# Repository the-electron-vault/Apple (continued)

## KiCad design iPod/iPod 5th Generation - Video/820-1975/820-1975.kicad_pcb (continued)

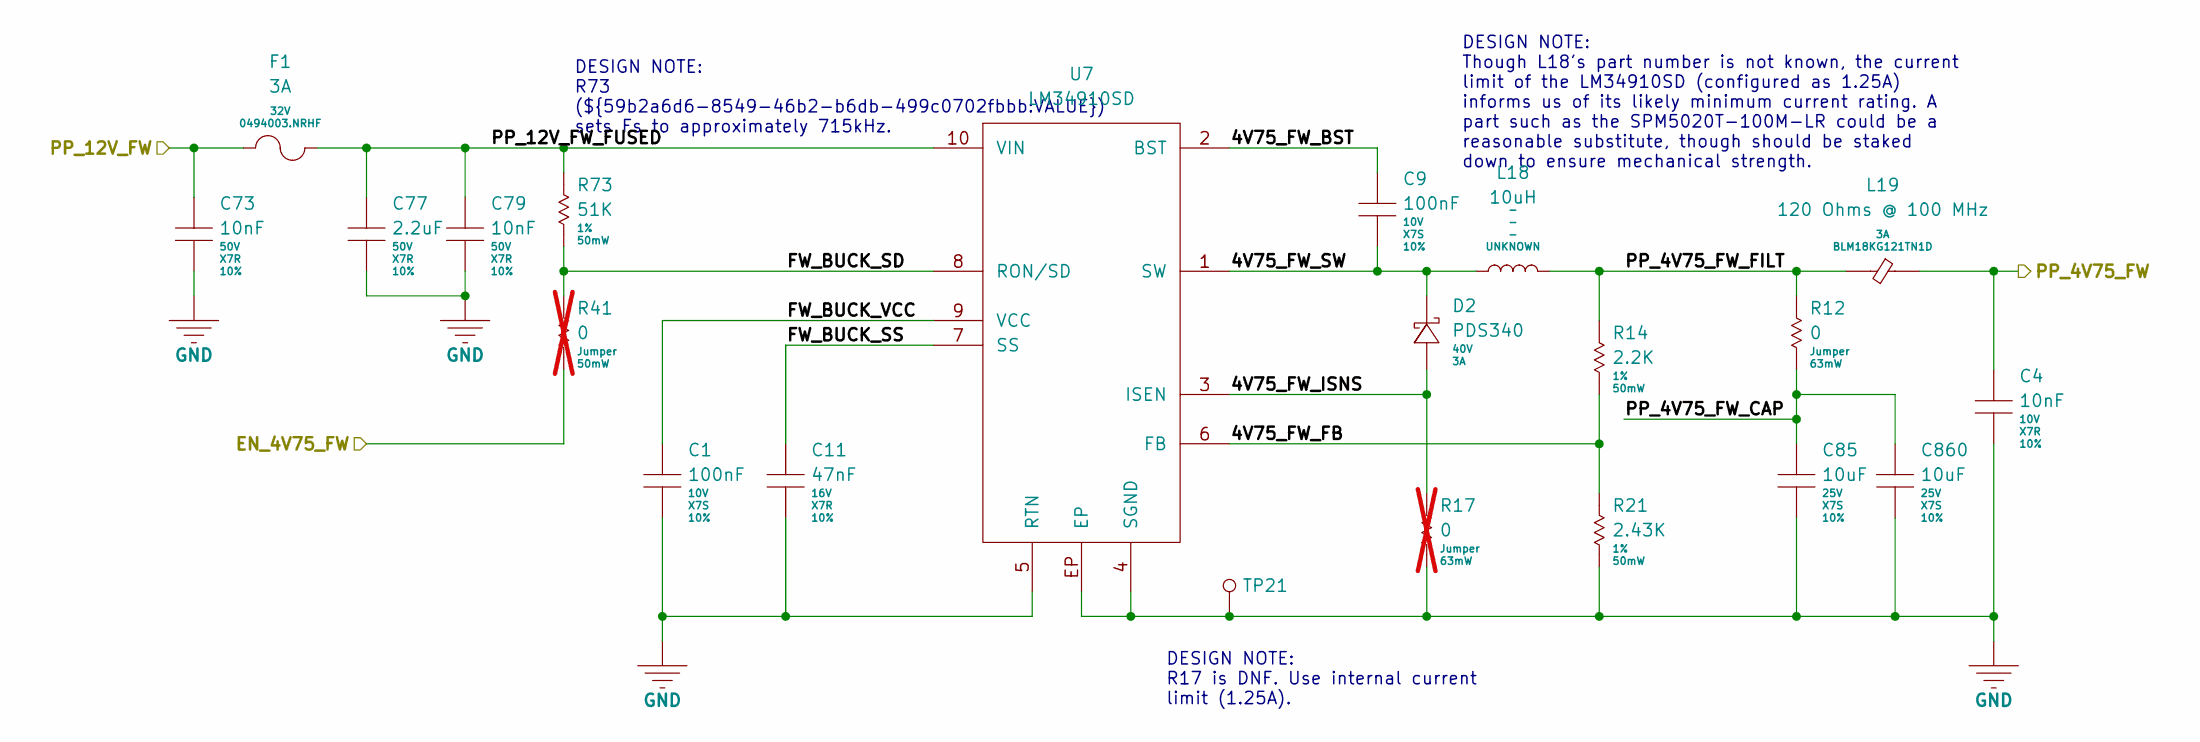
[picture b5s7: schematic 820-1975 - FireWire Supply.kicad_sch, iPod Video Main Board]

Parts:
C1, C9: 100nF; MLCC-0201; Voltage 10V; Tolerance 10%; Manufacturer Part Number GRM033C71A104KE14D
C4: 10nF; MLCC-0201; Voltage 10V; Tolerance 10%; Manufacturer Part Number GRM033R71A103KA01D
C11: 47nF; MLCC-0402; Voltage 16V; Tolerance 10%; Manufacturer Part Number GCM155R71C473KA37D
C73, C79: 10nF; MLCC-0603; Voltage 50V; Tolerance 10%; Manufacturer Part Number GCM188R71H103KA37D
C77: 2.2uF; MLCC-1206; Voltage 50V; Tolerance 10%; Manufacturer Part Number GCM31CR71H225KA55L
C85, C860: 10uF; MLCC-0805; Voltage 25V; Tolerance 10%; Manufacturer Part Number GRM21BC71E106KE11L
D2: PDS340; PowerDI-5; Voltage 40V; Manufacturer Part Number PDS340
F1: 3A; FUSE-0603; Voltage 32V; Manufacturer Part Number 0494003.NRHF
L18: 10uH; SUMIDA-UNKNOWN; Manufacturer Part Number UNKNOWN
L19: 120 Ohms @ 100 MHz; FB-0603; Manufacturer Part Number BLM18KG121TN1D
R12: 0; RES-0402; Tolerance Jumper; Manufacturer Part Number CRCW04020000Z0ED
R14: 2.2K; RES-0201; Tolerance 1%; Manufacturer Part Number CRCW02012K20FNED
R17: 0; RES-0402; Tolerance Jumper; Manufacturer Part Number CRCW04020000Z0ED; not fitted
R21: 2.43K; RES-0201; Tolerance 1%; Manufacturer Part Number CRCW02012K43FNED
R41: 0; RES-0201; Tolerance Jumper; Manufacturer Part Number CRCW02010000Z0ED; not fitted
R73: 51K; RES-0201; Tolerance 1%; Manufacturer Part Number CRCW020151K0FNED
TP21: TP; TP-SMT
U7: LM34910SD; DPR0010A; Manufacturer Part Number LM34910SD

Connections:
/Charger-and-3.3V-Supply/PP_4V75_FW: C4.1, L19.2; also elsewhere on the board
/Dock-Interface/PP_12V_FW: C73.1, F1.1; also elsewhere on the board
/FireWire-Supply/4V75_FW_BST: C9.1, U7.2 (BST)
/FireWire-Supply/4V75_FW_FB: R14.2, R21.1, U7.6 (FB)
/FireWire-Supply/4V75_FW_ISNS: D2.A, R17.1, U7.3 (ISEN)
/FireWire-Supply/4V75_FW_SW: C9.2, D2.K, L18.1, U7.1 (SW)
/FireWire-Supply/EN_4V75_FW: R41.2; also elsewhere on the board
/FireWire-Supply/FW_BUCK_SD: R41.1, R73.2, U7.8 (RON/SD)
/FireWire-Supply/FW_BUCK_SS: C11.1, U7.7 (SS)
/FireWire-Supply/FW_BUCK_VCC: C1.1, U7.9 (VCC)
/FireWire-Supply/PP_4V75_FW_CAP: C85.1, C860.1, R12.2
/FireWire-Supply/PP_4V75_FW_FILT: L18.2, L19.1, R12.1, R14.1
/FireWire-Supply/PP_12V_FW_FUSED: C77.1, C79.1, F1.2, R73.1, U7.10 (VIN)
GND: C1.2, C4.2, C11.2, C73.2, C77.2, C79.2, C85.2, C860.2, R17.2, R21.2, TP21.1, U7.4 (SGND), U7.5 (RTN), U7.EP; also elsewhere on the board

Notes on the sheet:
DESIGN NOTE: R73 (${59b2a6d6-8549-46b2-b6db-499c0702fbbb:VALUE}) sets Fs to approximately 715kHz.
DESIGN NOTE: R17 is DNF. Use internal current limit (1.25A).
DESIGN NOTE: Though L18's part number is not known, the current limit of the LM34910SD (configured as 1.25A) informs us of its likely minimum current rating. A part such as the SPM5020T-100M-LR could be a reasonable substitute, though should be staked down to ensure mechanical strength.

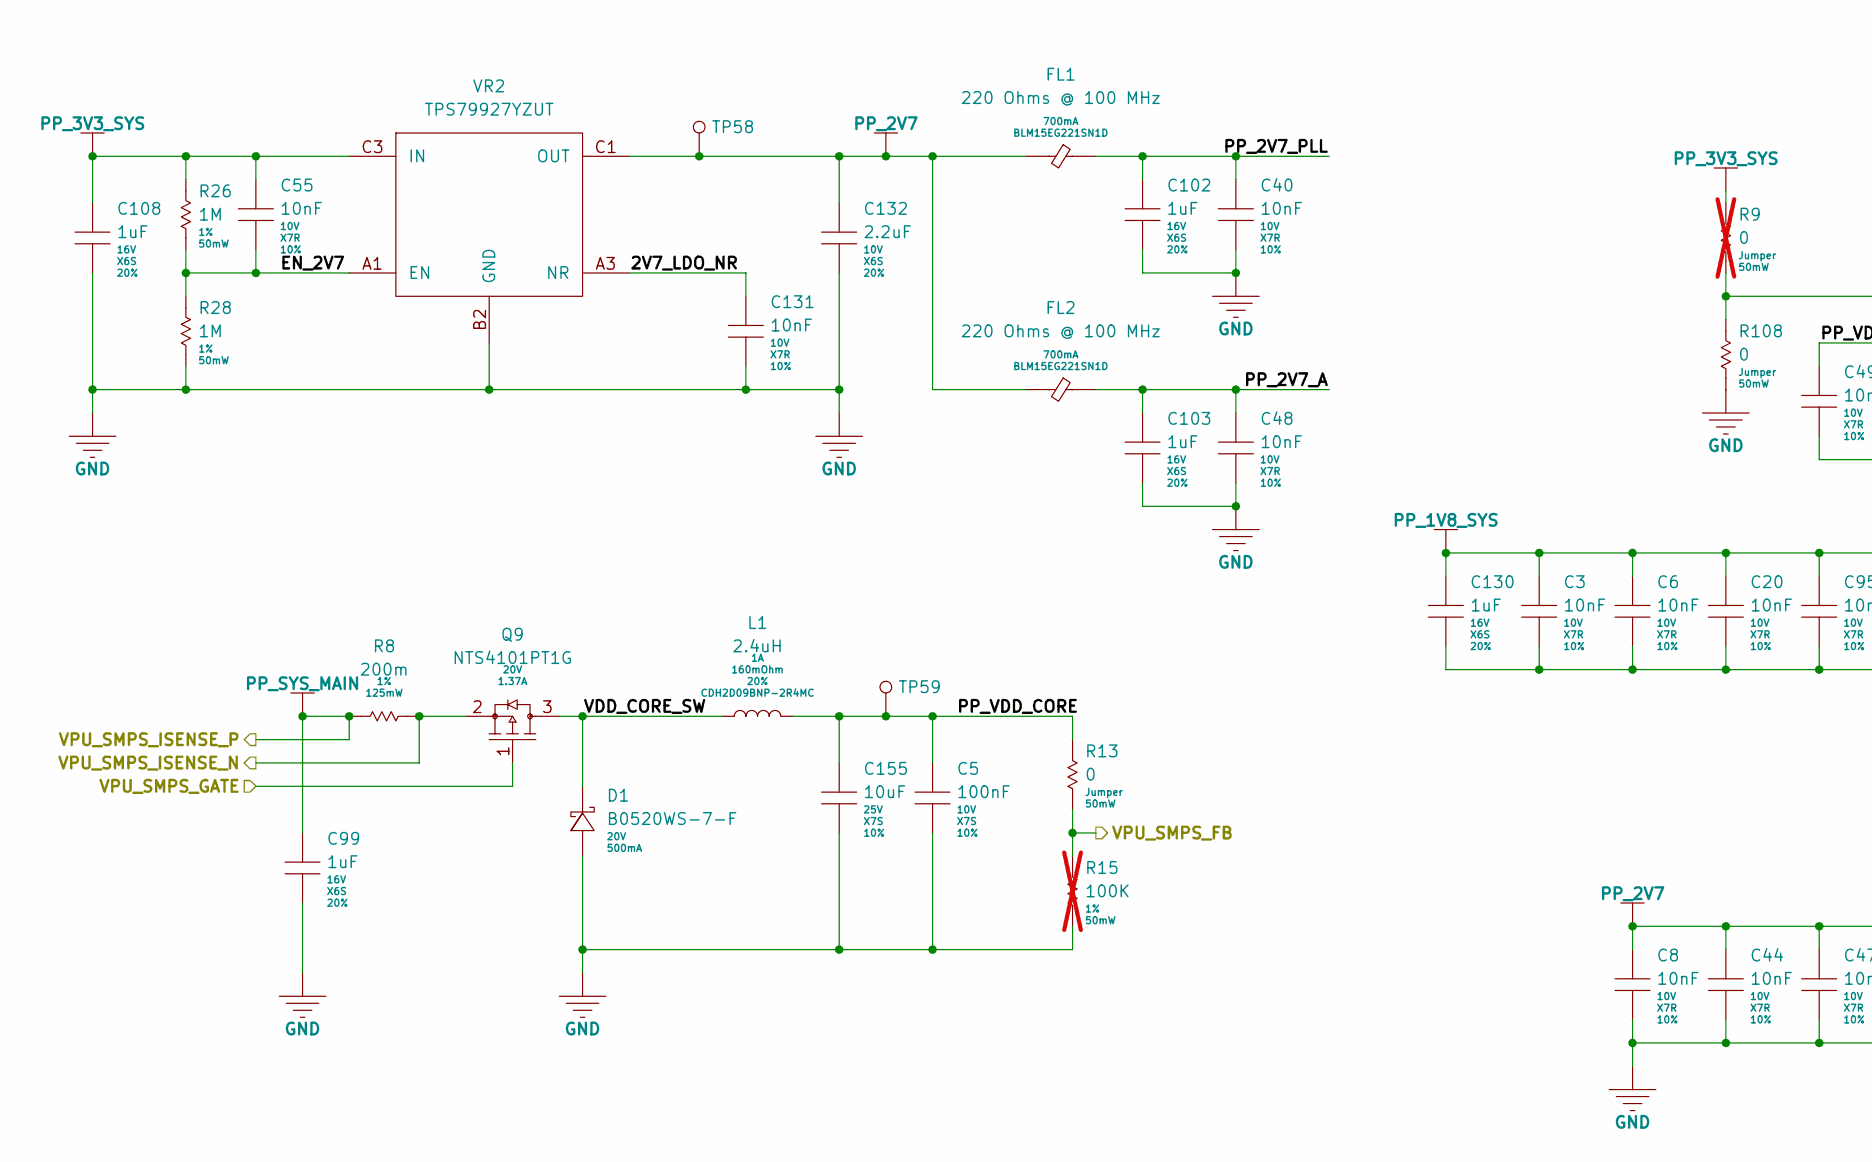
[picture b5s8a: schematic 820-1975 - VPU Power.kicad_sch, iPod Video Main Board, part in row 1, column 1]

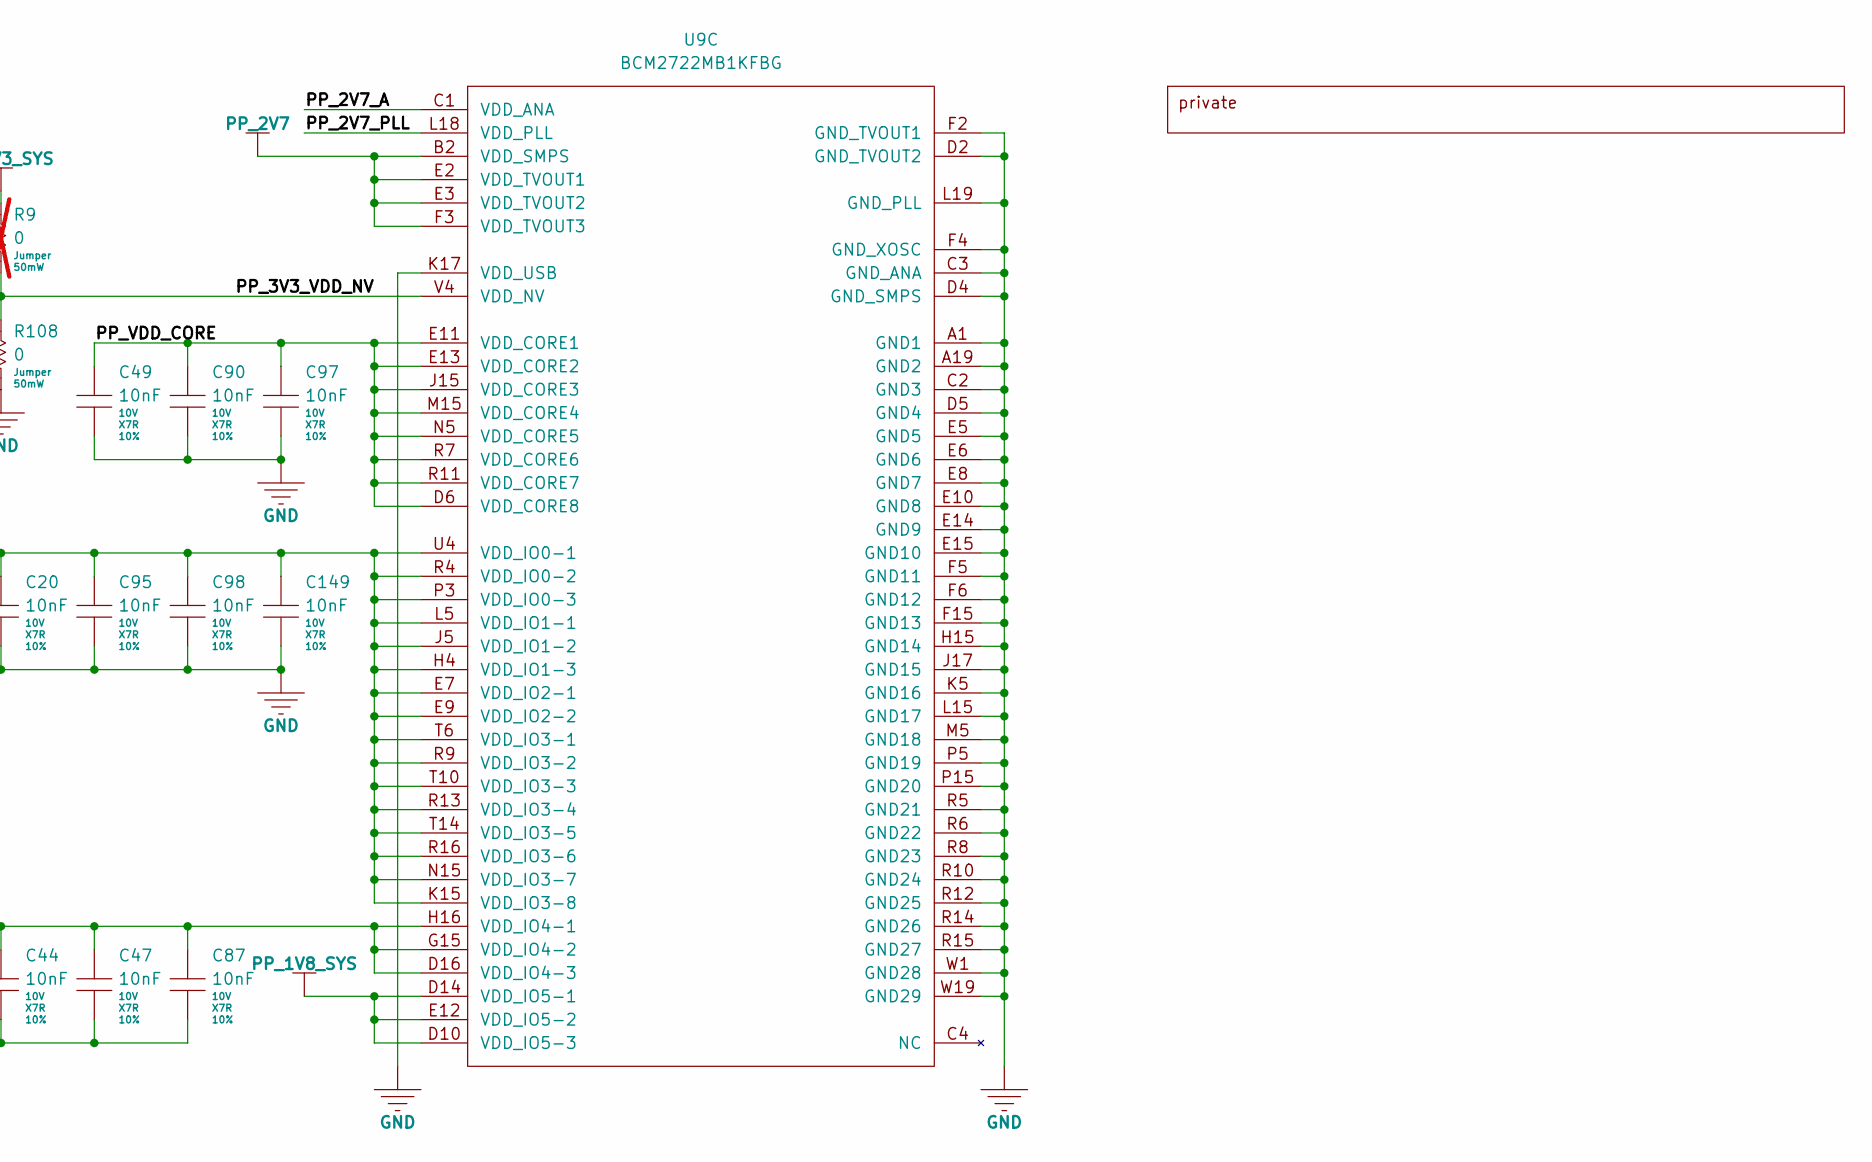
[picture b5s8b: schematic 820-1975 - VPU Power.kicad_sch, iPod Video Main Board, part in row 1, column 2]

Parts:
C3, C6, C8, C20, C40, C44, C47, C48, C49, C55, C87, C90, C95, C97, C98, C131, C149: 10nF; MLCC-0201; Voltage 10V; Tolerance 10%; Manufacturer Part Number GRM033R71A103KA01D
C5: 100nF; MLCC-0201; Voltage 10V; Tolerance 10%; Manufacturer Part Number GRM033C71A104KE14D
C99, C102, C103, C108, C130: 1uF; MLCC-0402; Voltage 16V; Tolerance 20%; Manufacturer Part Number GRM155C81C105ME11J
C132: 2.2uF; MLCC-0402; Voltage 10V; Tolerance 20%; Manufacturer Part Number GRM155C81A225ME44D
C155: 10uF; MLCC-0805; Voltage 25V; Tolerance 10%; Manufacturer Part Number GRM21BC71E106KE11L
D1: B0520WS-7-F; SOD-323; Voltage 20V; Manufacturer Part Number B0520WS-7-F
FL1, FL2: 220 Ohms @ 100 MHz; FB-0402; Manufacturer Part Number BLM15EG221SN1D
L1: 2.4uH; CDH2D09B; Tolerance 20%; Manufacturer Part Number CDH2D09BNP-2R4MC
Q9: NTS4101PT1G; SOT-323; Voltage 20V; Manufacturer Part Number NTS4101PT1G
R8: 200m; RES-0402; Tolerance 1%; Manufacturer Part Number RCWE0402R200FKEA
R9: 0; RES-0201; Tolerance Jumper; Manufacturer Part Number CRCW02010000Z0ED; not fitted
R13, R108: 0; RES-0201; Tolerance Jumper; Manufacturer Part Number CRCW02010000Z0ED
R15: 100K; RES-0201; Tolerance 1%; Manufacturer Part Number CRCW0201100KFNED; not fitted
R26, R28: 1M; RES-0201; Tolerance 1%; Manufacturer Part Number CRCW02011M00FNED
TP58, TP59: TP; TP-SMT
U9: BCM2722MB1KFBG; Manufacturer Part Number BCM2722MB1KFBG
VR2: TPS79927YZUT; TI-YZU0005; Manufacturer Part Number TPS79927YZUT

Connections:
/VPU-Power/2V7_LDO_NR: C131.1, VR2.A3 (NR)
/VPU-Power/EN_2V7: C55.2, R26.2, R28.1, VR2.A1 (EN)
/VPU-Power/PP_2V7_A: C48.1, C103.1, FL2.2, U9.C1 (VDD_ANA)
/VPU-Power/PP_2V7_PLL: C40.1, C102.1, FL1.2, U9.L18 (VDD_PLL)
/VPU-Power/PP_3V3_VDD_NV: R9.2, R108.1, U9.V4 (VDD_NV)
/VPU-Power/PP_VDD_CORE: C5.1, C49.1, C90.1, C97.1, C155.1, L1.2, R13.1, TP59.1, U9.D6 (VDD_CORE8), U9.E11 (VDD_CORE1), U9.E13 (VDD_CORE2), U9.J15 (VDD_CORE3), U9.M15 (VDD_CORE4), U9.N5 (VDD_CORE5), U9.R7 (VDD_CORE6), U9.R11 (VDD_CORE7)
/VPU-Power/VDD_CORE_SW: D1.K, L1.1, Q9.3 (D)
/VPU-Power/VPU_SMPS_FB: R13.2, R15.1; also elsewhere on the board
/VPU-Power/VPU_SMPS_GATE: Q9.1 (G); also elsewhere on the board
/VPU-Power/VPU_SMPS_ISENSE_N: Q9.2 (S), R8.2; also elsewhere on the board
GND: C3.2, C5.2, C6.2, C8.2, C20.2, C40.2, C44.2, C47.2, C48.2, C49.2, C87.2, C90.2, C95.2, C97.2, C98.2, C99.2, C102.2, C103.2, C108.2, C130.2, C131.2, C132.2, C149.2, C155.2, D1.A, R15.2, R28.2, R108.2, U9.A1 (GND1), U9.A19 (GND2), U9.C2 (GND3), U9.C3 (GND_ANA), U9.D2 (GND_TVOUT2), U9.D4 (GND_SMPS), U9.D5 (GND4), U9.E5 (GND5), U9.E6 (GND6), U9.E8 (GND7), U9.E10 (GND8), U9.E14 (GND9), U9.E15 (GND10), U9.F2 (GND_TVOUT1), U9.F4 (GND_XOSC), U9.F5 (GND11), U9.F6 (GND12), U9.F15 (GND13), U9.H15 (GND14), U9.J17 (GND15), U9.K5 (GND16), U9.K17 (VDD_USB), U9.L15 (GND17), U9.L19 (GND_PLL), U9.M5 (GND18), U9.P5 (GND19), U9.P15 (GND20), U9.R5 (GND21), U9.R6 (GND22), U9.R8 (GND23), U9.R10 (GND24), U9.R12 (GND25), U9.R14 (GND26), U9.R15 (GND27), U9.W1 (GND28), U9.W19 (GND29), VR2.B2 (GND); also elsewhere on the board
PP_1V8_SYS: C3.1, C6.1, C20.1, C95.1, C98.1, C130.1, C149.1, U9.D10 (VDD_IO5-3), U9.D14 (VDD_IO5-1), U9.E7 (VDD_IO2-1), U9.E9 (VDD_IO2-2), U9.E12 (VDD_IO5-2), U9.H4 (VDD_IO1-3), U9.J5 (VDD_IO1-2), U9.K15 (VDD_IO3-8), U9.L5 (VDD_IO1-1), U9.N15 (VDD_IO3-7), U9.P3 (VDD_IO0-3), U9.R4 (VDD_IO0-2), U9.R9 (VDD_IO3-2), U9.R13 (VDD_IO3-4), U9.R16 (VDD_IO3-6), U9.T6 (VDD_IO3-1), U9.T10 (VDD_IO3-3), U9.T14 (VDD_IO3-5), U9.U4 (VDD_IO0-1); also elsewhere on the board
PP_2V7: C8.1, C44.1, C47.1, C87.1, C132.1, FL1.1, FL2.1, TP58.1, U9.B2 (VDD_SMPS), U9.D16 (VDD_IO4-3), U9.E2 (VDD_TVOUT1), U9.E3 (VDD_TVOUT2), U9.F3 (VDD_TVOUT3), U9.G15 (VDD_IO4-2), U9.H16 (VDD_IO4-1), VR2.C1 (OUT); also elsewhere on the board
PP_3V3_SYS: C55.1, C108.1, R9.1, R26.1, VR2.C3 (IN); also elsewhere on the board
PP_SYS_MAIN: C99.1, R8.1; also elsewhere on the board

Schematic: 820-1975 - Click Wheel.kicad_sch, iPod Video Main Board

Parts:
C39, C41: 100nF; MLCC-0201; Voltage 10V; Tolerance 10%; Manufacturer Part Number GRM033C71A104KE14D
C52: 1nF; MLCC-0201; Voltage 25V; Tolerance 10%; Manufacturer Part Number GRM033R71E102KA01J
C141: 4.7uF; MLCC-0603; Voltage 10V; Tolerance 10%; Manufacturer Part Number GRM188C71A475KE11D
J5: FF12-13A-R11AL-3H; Manufacturer Part Number FF12-13A-R11AL-3H
Q5: BSS84DW-7-F; SOT-363; Voltage 50V; Manufacturer Part Number BSS84DW-7-F
R2: 1M; RES-0201; Tolerance 1%; Manufacturer Part Number CRCW02011M00FNED
R3: 2.2M; RES-0201; Tolerance 1%; Manufacturer Part Number CRCW02012M20FNED
R44: 100K; RES-0201; Tolerance 1%; Manufacturer Part Number CRCW0201100KFNED
R61: 10K; RES-0201; Tolerance 1%; Manufacturer Part Number CRCW020110K0FNED
R86: 0; RES-0201; Tolerance Jumper; Manufacturer Part Number CRCW02010000Z0ED; not fitted
R87: 220K; RES-0201; Tolerance 1%; Manufacturer Part Number CRCW0201220KFNED
R97: 0; RES-0201; Tolerance Jumper; Manufacturer Part Number CRCW02010000Z0ED
R100, R101, R102, R103: 18K; RES-0201; Tolerance 1%; Manufacturer Part Number CRCW020118K0FKED
R142: 10; RES-0201; Tolerance 1%; Manufacturer Part Number CRCW020110R0FNED
S100, S101, S102, S103, S104: SOP-112HST; SOP-11xHST; Manufacturer Part Number SOP-112HST
TP87, TP88, TP89, TP90, TP91, TP92, TP93, TP94, TP95, TP96, TP97, TP98, TP99, TP100, TP101: TP; TP-SMT
U19: SN74LVC1G32YZPR; TI-YZP0005; Manufacturer Part Number SN74LVC1G32YZPR

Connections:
/CODEC/HOLD: C52.1, R3.1, R44.1; also elsewhere on the board
/Charger-and-3.3V-Supply/RESET_SYS: C41.1, R61.1; also elsewhere on the board
/Click-Wheel/BTN_FF_L: J5.5, S103.3, S103.4, TP96.1
/Click-Wheel/BTN_MENU_L: J5.4, S102.3, S102.4, TP97.1
/Click-Wheel/BTN_PP_L: J5.6, S104.3, S104.4, TP95.1
/Click-Wheel/BTN_RW_L: J5.3, S101.3, S101.4, TP98.1
/Click-Wheel/BTN_SEL_L: J5.2, S100.3, S100.4, TP99.1
/Click-Wheel/CW_CLK: U19.4 (Y); also elsewhere on the board
/Click-Wheel/CW_GATE_CLK: J5.12, R101.2, TP89.1, U19.1 (A)
/Click-Wheel/CW_PIN7: J5.7, R102.2, TP94.1; also elsewhere on the board
/Click-Wheel/CW_SDI: J5.8, R103.2, TP93.1; also elsewhere on the board
/Click-Wheel/CW_SDO: J5.11, R100.2, TP90.1; also elsewhere on the board
/Click-Wheel/EN_CW_PWR_L: Q5.2 (G1), Q5.5 (G2), R44.2
/Click-Wheel/PMU_EXTON: J5.10, TP91.1; also elsewhere on the board
/Click-Wheel/PP_VDDIO_CW_FET: Q5.4 (S2), R86.2, R97.2
/Click-Wheel/PP_VDD_CW: Q5.6 (D1), R142.1
/Click-Wheel/PP_VDD_CW_CONN: C141.1, J5.13, R142.2, TP87.1
/Click-Wheel/RESET_SYS_CW: J5.9, R61.2, R87.1, TP92.1
GND: C39.2, C41.2, C52.2, C141.2, J5.1, R2.2, R3.2, R87.2, S100.1, S100.2, S101.1, S101.2, S102.1, S102.2, S103.1, S103.2, S104.1, S104.2, TP100.1, TP101.1, U19.2 (B), U19.3 (GND); also elsewhere on the board
PP_3V3_SYS: C39.1, R86.1, U19.5 (VCC); also elsewhere on the board
PP_3V_LCD: R97.1; also elsewhere on the board
PP_SYS_MAIN: Q5.1 (S1); also elsewhere on the board
PP_VDDIO_CW: Q5.3 (D2), R2.1, R100.1, R101.1, R102.1, R103.1, TP88.1; also elsewhere on the board

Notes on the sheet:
DESIGN NOTE: CW_SDO only outputs data when shorted to CW_SDI (when operating clickwheel standalone). The purpose of J5-7 is not known.
DESIGN NOTE: RESET_SYS_CW pulses high for 500ms when Menu and Select are held for 5 seconds. Menu button *must* detect finger on clickwheel. Simply pressing the underlying buttons is not sufficient. PMU_EXTON pulses high for 20ms when Menu or Select is pressed.

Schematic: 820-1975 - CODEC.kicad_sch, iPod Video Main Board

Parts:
C42, C127, C148: 10nF; MLCC-0201; Voltage 10V; Tolerance 10%; Manufacturer Part Number GRM033R71A103KA01D
C84, C86, C100, C101: 10uF; KYOCERA-TAC-L; Voltage 6.3V; Tolerance 20%; Manufacturer Part Number TACL106M006RTA
C89, C925, C926: 100nF; MLCC-0201; Voltage 10V; Tolerance 10%; Manufacturer Part Number GRM033C71A104KE14D
C96: 4.7uF; MLCC-0603; Voltage 10V; Tolerance 10%; Manufacturer Part Number GRM188C71A475KE11D
C138: 2.2uF; MLCC-0603; Voltage 25V; Tolerance 10%; Manufacturer Part Number GRM188C71E225KE11D
C140, C150: 4.7uF; VISHAY-TMCJ; Voltage 6.3V; Tolerance 20%; Manufacturer Part Number TMCJ0J475MTRF
C145, C146: 150uF; VISHAY-595D-B; Voltage 4V; Tolerance 20%; Manufacturer Part Number 595D157X0004B2T
J1: FH26W-13S-0.3SHW; Manufacturer Part Number FH26W-13S-0.3SHW
Q2: MMDT3946-7-F; SOT-363; Voltage 40V; Manufacturer Part Number MMDT3946-7-F
R23, R123: 0; RES-0201; Tolerance Jumper; Manufacturer Part Number CRCW02010000Z0ED; not fitted
R24: 10K; RES-0201; Tolerance 1%; Manufacturer Part Number CRCW020110K0FNED
R39, R129: 0; RES-0201; Tolerance Jumper; Manufacturer Part Number CRCW02010000Z0ED
R84: 33; RES-0201; Tolerance 1%; Manufacturer Part Number CRCW020133R0FNED
R133: 1M; RES-0201; Tolerance 1%; Manufacturer Part Number CRCW02011M00FNED
R134, R194, R195, R196, R197: 100K; RES-0201; Tolerance 1%; Manufacturer Part Number CRCW0201100KFNED
R146: 1K; RES-0201; Tolerance 1%; Manufacturer Part Number CRCW02011K00FNED
R147: 270; RES-0201; Tolerance 1%; Manufacturer Part Number CRCW0201270RFKED
R190, R191, R192, R193: 100; RES-0201; Tolerance 1%; Manufacturer Part Number CRCW0201100RFKED
R915: 47; RES-0201; Tolerance 1%; Manufacturer Part Number CRCW020147R0FNED
TP102, TP103, TP104, TP105, TP106, TP107: TP; TP-SMT
U5: WM8758CBGEFL; Manufacturer Part Number WM8758CBGEFL
U8, U13, U14: SN74LVC1G32YZPR; TI-YZP0005; Manufacturer Part Number SN74LVC1G32YZPR

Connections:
/CODEC/AUDCONN_TIPDET: C138.1, R133.2, R134.1; also elsewhere on the board
/CODEC/AUDCONN_TIPDET_SW: J1.1, R134.2, TP102.1
/CODEC/AUDCONN_VID_COMP: J1.10; also elsewhere on the board
/CODEC/CODEC_CSB: R123.2, R129.1, U5.15 (CSB)
/CODEC/CODEC_MCLK: R84.1; also elsewhere on the board
/CODEC/CODEC_MCLK_R: R84.2, TP105.1, U5.11 (MCLK)
/CODEC/CODEC_VMID: C96.1, U5.27 (VMID)
/CODEC/EN_I2S_VPU_L: R23.1; also elsewhere on the board
/CODEC/EN_I2S_VPU_R_L: R23.2, R39.1, U8.2 (B), U13.2 (B)
/CODEC/HOLD: J1.13, TP106.1; also elsewhere on the board
/CODEC/HOLD_SW_PU: J1.12, R24.2, TP104.1
/CODEC/HP_COM: C150.1, U5.19 (HP_COM)
/CODEC/HP_COM_CONN: C150.2, J1.8
/CODEC/HP_L: C145.1, U5.30 (LOUT1)
/CODEC/HP_L_CONN: C145.2, J1.5
/CODEC/HP_R: C146.1, U5.29 (ROUT1)
/CODEC/HP_R_CONN: C146.2, J1.6
/CODEC/I2C_SCL: U5.16 (SCLK); also elsewhere on the board
/CODEC/I2C_SDA: U5.17 (SDIN); also elsewhere on the board
/CODEC/I2S_DOUT: U5.10 (DACDAT), U14.4 (Y)
/CODEC/I2S_MPU_BCLK: U5.8 (BCLK), U13.1 (A); also elsewhere on the board
/CODEC/I2S_MPU_DIN: U5.9 (ADCDAT); also elsewhere on the board
/CODEC/I2S_MPU_DOUT: U14.2 (B); also elsewhere on the board
/CODEC/I2S_MPU_LRC: U5.7 (LRC), U8.1 (A); also elsewhere on the board
/CODEC/I2S_VPU_BCLK: U13.4 (Y); also elsewhere on the board
/CODEC/I2S_VPU_DOUT: U14.1 (A); also elsewhere on the board
/CODEC/I2S_VPU_LRC: U8.4 (Y); also elsewhere on the board
/CODEC/LINEIN_CAP_L: C101.2, R192.1, R195.1
/CODEC/LINEIN_CAP_R: C100.2, R193.1, R194.1
/CODEC/LINEIN_L: R192.2; also elsewhere on the board
/CODEC/LINEIN_R: R193.2; also elsewhere on the board
/CODEC/LINEOUT_CAP_L: C86.2, R190.1, R197.1
/CODEC/LINEOUT_CAP_R: C84.2, R191.1, R196.1
/CODEC/LINEOUT_COM: C140.2, R196.2, R197.2, R915.1; also elsewhere on the board
/CODEC/LINEOUT_L: R190.2; also elsewhere on the board
/CODEC/LINEOUT_R: R191.2; also elsewhere on the board
/CODEC/LIN_L: C101.1, U5.3 (L2)
/CODEC/LIN_R: C100.1, U5.6 (R2)
/CODEC/LOUT_COM: C140.1, U5.20 (LINE_COM)
/CODEC/LOUT_L: C86.1, U5.25 (LOUT2)
/CODEC/LOUT_R: C84.1, U5.23 (ROUT2)
/CODEC/PP_3V_CODEC: C89.1, U5.26 (AVDD2), U5.31 (AVDD1); also elsewhere on the board
/CODEC/SPKR: J1.2, Q2.1 (E2), Q2.3 (C1), TP103.1
/CODEC/SPKR_DRV: C148.1, Q2.5 (B1), Q2.6 (C2), R147.2
/CODEC/SPKR_DRV_BASE: C148.2, Q2.2 (B2), R146.2
/CODEC/SPKR_OUT: R146.1; also elsewhere on the board
GND: C42.2, C89.2, C96.2, C127.2, C138.2, C925.2, C926.2, J1.3, J1.4, J1.7, J1.9, J1.11, R39.2, R129.2, R194.2, R195.2, R915.2, TP107.1, U5.12 (DGND), U5.18 (MODE), U5.24 (AGND2), U5.28 (AGND1), U5.EP (AGND3), U8.3 (GND), U13.3 (GND), U14.3 (GND); also elsewhere on the board
PP_1V8_SYS: C925.1, U5.13 (DCVDD); also elsewhere on the board
PP_2V7: C127.1, U8.5 (VCC), U13.5 (VCC); also elsewhere on the board
PP_3V3_SYS: C42.1, C926.1, Q2.4 (E1), R123.1, R133.1, R147.1, U5.14 (DBVDD), U14.5 (VCC); also elsewhere on the board
PP_SYS_MAIN: R24.1; also elsewhere on the board

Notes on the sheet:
DESIGN NOTE: Headphone/Hold flex uses PUI Audio SMT-0540-T-10-R speaker.
Write: 0x34 Read: 0x35
Audio CODEC
DESIGN NOTE: Q2 configured as a Sziklai pair.
DESIGN NOTE: Tip detect switch is normally closed to left channel (tip) contact. Headphone/Hold flex has 3.9k pull-downs from each channel to COM/GND. Thus AUDCONN_TIPDET is low when no jack is inserted, and high when inserted or flex is disconnected.
GND
U13-1
HOLD SWITCH COM
SPEAKER+
JACK TIP SWITCH
U8-1
JACK SLEEVE SWITCH
HOLD SWITCH
LEFT (TIP)
SPEAKER-
COM (SLEEVE)
RIGHT (RING)

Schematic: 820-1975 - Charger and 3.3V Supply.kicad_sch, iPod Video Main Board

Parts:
C60, C135: 1uF; MLCC-0402; Voltage 16V; Tolerance 20%; Manufacturer Part Number GRM155C81C105ME11J
C61: 10nF; MLCC-0201; Voltage 10V; Tolerance 10%; Manufacturer Part Number GRM033R71A103KA01D
C82, C104: 47uF; KEMET-T490T; Voltage 6V; Tolerance 20%; Manufacturer Part Number T490T476M006ATE800
C88, C94: 10uF; MLCC-0805; Voltage 25V; Tolerance 10%; Manufacturer Part Number GRM21BC71E106KE11L
C109: 10nF; MLCC-0201; Voltage 10V; Tolerance 10%; Manufacturer Part Number GRM033R71A103KA01D; not fitted
C119, C121: 100nF; MLCC-0201; Voltage 10V; Tolerance 10%; Manufacturer Part Number GRM033C71A104KE14D
C134: 68nF; MLCC-0402; Voltage 16V; Tolerance 10%; Manufacturer Part Number GCM155R71C683KA55D
D9, D10: B0520WS-7-F; SOD-323; Voltage 20V; Manufacturer Part Number B0520WS-7-F
J6: FF15A-5-S14A; Manufacturer Part Number FF15A-5-S14A
L17: 10uH; SUMIDA-UNKNOWN; Manufacturer Part Number UNKNOWN
L43: 120 Ohms @ 100 MHz; FB-0603; Manufacturer Part Number BLM18KG121TN1D
Q1: CMLT3904E; SOT563; Voltage 40V; Manufacturer Part Number CMLT3904E
Q3, Q17: CMLDM7002A; SOT563; Voltage 60V; Manufacturer Part Number CMLDM7002A
Q4: NTS4101PT1G; SOT-323; Voltage 20V; Manufacturer Part Number NTS4101PT1G
R1: 470K; RES-0201; Tolerance 1%; Manufacturer Part Number CRCW0201470KFNED
R4, R37, R112: 47K; RES-0201; Tolerance 1%; Manufacturer Part Number CRCW020147K0FNED
R6, R20: 0; RES-0402; Tolerance Jumper; Manufacturer Part Number CRCW04020000Z0ED
R33, R392, R393: 1M; RES-0201; Tolerance 1%; Manufacturer Part Number CRCW02011M00FNED
R35, R55, R58, R65, R82: 100K; RES-0201; Tolerance 1%; Manufacturer Part Number CRCW0201100KFNED
R36: 3K; RES-0201; Tolerance 1%; Manufacturer Part Number CRCW02013K00FNED
R54: 1K; RES-0201; Tolerance 1%; Manufacturer Part Number CRCW02011K00FNED
R64: 0; RES-0201; Tolerance Jumper; Manufacturer Part Number CRCW02010000Z0ED
R71, R76: 1K; RES-0402; Tolerance 1%; Manufacturer Part Number CRCW04021K00FKED; not fitted
R77: 107K; RES-0201; Tolerance 1%; Manufacturer Part Number CRCW0201107KFNED
R78: 66.5K; RES-0201; Tolerance 1%; Manufacturer Part Number CRCW020166K5FNED
R79: 220K; RES-0201; Tolerance 1%; Manufacturer Part Number CRCW0201220KFNED
R80: 680; RES-0201; Tolerance 1%; Manufacturer Part Number CRCW0201680RFKED
R109: 2K; RES-0201; Tolerance 1%; Manufacturer Part Number CRCW02012K00FNED
R110: 150K; RES-0201; Tolerance 1%; Manufacturer Part Number CRCW0201150KFNED
R111: 10K; RES-0201; Tolerance 1%; Manufacturer Part Number CRCW020110K0FNED
R113: 25.5K; RES-0201; Tolerance 1%; Manufacturer Part Number CRCW020125K5FNED
R114: 12K; RES-0201; Tolerance 1%; Manufacturer Part Number CRCW020112K0FNED
R115, R116: 3.3K; RES-0201; Tolerance 1%; Manufacturer Part Number CRCW02013K30FNED
TP22, TP23, TP24, TP25, TP26, TP27, TP28, TP29: TP; TP-SMT
U2: LTC4066EUF#PBF; LTC4066EUF; Manufacturer Part Number LTC4066EUF#PBF
U6: TEA1211HN; VQFN-32-0.5; Manufacturer Part Number TEA1211HN
U11: SN74LVC1G32YZPR; TI-YZP0005; Manufacturer Part Number SN74LVC1G32YZPR

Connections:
/Charger-and-3.3V-Supply/3V3_BB_CAP: C82.1, R6.2, R20.2
/Charger-and-3.3V-Supply/3V3_BB_ILIM: R80.1, U6.30 (ILIM)
/Charger-and-3.3V-Supply/3V3_BB_LXA: D10.K, L17.1, U6.1 (LXA), U6.3 (LXA), U6.4 (LXA), U6.10 (LXA), U6.11 (LXA)
/Charger-and-3.3V-Supply/3V3_BB_LXB: D9.A, L17.2, U6.14 (LXB), U6.15 (LXB), U6.21 (LXB), U6.22 (LXB), U6.24 (LXB)
/Charger-and-3.3V-Supply/3V3_SYS_BOOST: Q3.6 (D1), R33.2
/Charger-and-3.3V-Supply/3V3_SYS_DISCHG: Q1.5 (B2), R82.2
/Charger-and-3.3V-Supply/3V3_SYS_DISCHG_L: Q1.3 (C2), R54.2
/Charger-and-3.3V-Supply/3V3_SYS_FB: R33.1, R77.2, R78.1, U6.27 (FB)
/Charger-and-3.3V-Supply/4V75_FW_PRES: R55.2, U11.1 (A)
/Charger-and-3.3V-Supply/5V_USB_PRES: R58.2, U11.2 (B)
/Charger-and-3.3V-Supply/BAT_DISCHG_L: Q3.3 (D2), R71.2
/Charger-and-3.3V-Supply/BAT_DISCHG_RES: R71.1, R76.2
/Charger-and-3.3V-Supply/BAT_NTC: J6.3, R114.2, R116.1, TP26.1, U2.14 (NTC)
/Charger-and-3.3V-Supply/CHG_ACPR_3V3_L: Q1.6 (C1), R4.2; also elsewhere on the board
/Charger-and-3.3V-Supply/CHG_ACPR_BASE: Q1.2 (B1), R1.2
/Charger-and-3.3V-Supply/CHG_ACPR_L: Q1.1 (E1), Q4.1 (G), R115.2, U2.17 (~ACPR)
/Charger-and-3.3V-Supply/CHG_CLDIS: U2.10 (CLDIS); also elsewhere on the board
/Charger-and-3.3V-Supply/CHG_CLPROG: R109.1, U2.22 (CLPROG)
/Charger-and-3.3V-Supply/CHG_DET: U11.4 (Y); also elsewhere on the board
/Charger-and-3.3V-Supply/CHG_DISABLE: Q17.1 (G1), R392.1; also elsewhere on the board
/Charger-and-3.3V-Supply/CHG_HPWR: U2.13 (HPWR); also elsewhere on the board
/Charger-and-3.3V-Supply/CHG_ISTAT: C60.1, R36.1, U2.24 (ISTAT); also elsewhere on the board
/Charger-and-3.3V-Supply/CHG_POL: R37.2, U2.19 (POL); also elsewhere on the board
/Charger-and-3.3V-Supply/CHG_PROG: R110.1, U2.23 (PROG)
/Charger-and-3.3V-Supply/CHG_STAT_L: R112.2, U2.18 (~CHRG); also elsewhere on the board
/Charger-and-3.3V-Supply/CHG_SUSP: Q17.4 (G2), R393.1; also elsewhere on the board
/Charger-and-3.3V-Supply/CHG_SUSP_L: Q17.3 (D2), R116.2
/Charger-and-3.3V-Supply/CHG_TIMER: C61.1, C134.1, Q17.6 (D1), TP25.1, U2.21 (TIMER)
/Charger-and-3.3V-Supply/CHG_USB_SUSP: U2.11 (SUSP); also elsewhere on the board
/Charger-and-3.3V-Supply/CHG_VNTC: R114.1, U2.15 (VNTC)
/Charger-and-3.3V-Supply/CHG_WALL: R111.1, R113.2, U2.20 (WALL)
/Charger-and-3.3V-Supply/EN_3V3_VDD_L: C109.1, R79.2, U6.28 (SHDWN); also elsewhere on the board
/Charger-and-3.3V-Supply/EN_BAT_DISCHG: R64.1; also elsewhere on the board
/Charger-and-3.3V-Supply/EN_BAT_DISCHG_R: Q3.4 (G2), R64.2, R65.1
/Charger-and-3.3V-Supply/PP_3V3_BB: C121.1, D9.K, L43.1, R6.1, R20.1, R77.1, U6.23 (OUT), U6.25 (OUT), U6.26 (OUT)
/Charger-and-3.3V-Supply/PP_4V75_FW: Q4.3 (D), R55.1, R113.1; also elsewhere on the board
/Charger-and-3.3V-Supply/PP_5V_USB: C135.1, R58.1, U2.9 (IN); also elsewhere on the board
/Charger-and-3.3V-Supply/RESET_SYS: R82.1; also elsewhere on the board
GND: C60.2, C61.2, C82.2, C88.2, C94.2, C104.2, C109.2, C119.2, C121.2, C134.2, C135.2, D10.A, J6.4, J6.5, Q1.4 (E2), Q3.2 (S1), Q3.5 (S2), Q17.2 (S1), Q17.5 (S2), R35.2, R36.2, R65.2, R78.2, R80.2, R109.2, R110.2, R111.2, R392.2, R393.2, TP27.1, TP29.1, U2.12 (SHDN), U2.16 (GND), U2.EP (GND), U6.5 (GND), U6.7 (GND), U6.9 (GND), U6.12 (SCL), U6.13 (SDA), U6.16 (GND), U6.18 (GND), U6.20 (GND), U6.29 (SYNC/PWM), U6.EP (GND), U11.3 (GND); also elsewhere on the board
PP_3V3_HDD: Q3.1 (G1), R35.1; also elsewhere on the board
PP_3V3_SYS: C88.1, L43.2, R1.1, R4.1, R37.1, R54.1, R112.1, TP23.1, TP28.1; also elsewhere on the board
PP_SYS_MAIN: C94.1, C104.1, C119.1, Q4.2 (S), R79.1, R115.1, TP22.1, U2.1 (OUT), U2.3 (OUT), U2.8 (OUT), U6.2 (IN), U6.31 (IN), U6.32 (IN), U11.5 (VCC); also elsewhere on the board
PP_VBAT: J6.1, J6.2, R76.1, TP24.1, U2.2 (BAT), U2.4 (BAT), U2.5 (BAT); also elsewhere on the board

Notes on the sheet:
DESIGN NOTE: R110 (${6f7116db-934f-4571-9cb8-411f8b07028b:VALUE}) programs charge current to 333mA. R109 (${35cf32a8-cd35-4bd3-a215-247185fbe9b5:VALUE}) programs input current limit to 500mA. R36 (${f6098eaa-e9bf-45ef-af6e-ba967c35c4b5:VALUE}) programs charge terminate current to 33.3mA. C61 (${505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
DESIGN NOTE: The purpose of Q3B is also not clear. The values for R76 and R71 are simply placeholders as they are DNF on the actual board. Q3B is likely enabled by a GPO on the PMU, so its function is anybody's guess without having acess to firmware or probing the line during operation. Best guess 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
DESIGN NOTE: R116 (${3a281ace-e17d-441f-a95c-985144424278:VALUE}) forces the charger to register a hot NTC condition. This is likely used to suspend charging without clearing the charge timer. This is as opposed to the SUSP pin, which conditionally clears the timer unless the wall supply is present.
DESIGN NOTE: CHG_HPWR:0 = 100mA, 1 = 500mA
DESIGN NOTE: Q1B's collector doesn't connect to anything outside of R54. Best guess is this is to bleed off charge from C82 and the rest of the capacitance distributed across PP_3V3_SYS to enforce rail sequencing.
DESIGN NOTE: PP_SYS_MAIN voltages: USB Powered: 5V (TYP) FW Powered: 4.75V (TYP) Battery Powered: 3.2V ~ 4.3V
DESIGN NOTE: Though L17's part number is not known, the current limit of the TEA1211 (configured as 1.83A) informs us of its likely minimum current rating. A part such as the SPM5020T-100M-LR could be a reasonable substitute, though should be staked down to ensure mechanical strength.
DESIGN NOTE: R80 (${a718fab9-4d0c-4e38-bcdc-22e483c61845:VALUE}) programs peak input current to 1.83A.
DESIGN NOTE: It's not entirely clear why, but Q3A will cause PP_3V3_SYS to increase from 3.261V to 3.395V when PP_3V3_HDD is enabled.

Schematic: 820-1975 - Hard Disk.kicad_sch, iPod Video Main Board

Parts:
C12: 100nF; MLCC-0201; Voltage 10V; Tolerance 10%; Manufacturer Part Number GRM033C71A104KE14D
C13: 22nF; MLCC-0402; Voltage 50V; Tolerance 10%; Manufacturer Part Number GRM155R71H223KA12D
C14, C58: 10nF; MLCC-0201; Voltage 10V; Tolerance 10%; Manufacturer Part Number GRM033R71A103KA01D
J4: FH26W-35S-0.3SHW; Manufacturer Part Number FH26W-35S-0.3SHW
Q11: NTS4101PT1G; SOT-323; Voltage 20V; Manufacturer Part Number NTS4101PT1G
Q45: CMLDM7002A; SOT563; Voltage 60V; Manufacturer Part Number CMLDM7002A
R22: 100; RES-0201; Tolerance 1%; Manufacturer Part Number CRCW0201100RFKED
R25: 470K; RES-0201; Tolerance 1%; Manufacturer Part Number CRCW0201470KFNED
R27: 47K; RES-0201; Tolerance 1%; Manufacturer Part Number CRCW020147K0FNED
R53: 10K; RES-0201; Tolerance 1%; Manufacturer Part Number CRCW020110K0FNED
R56: 4.7K; RES-0201; Tolerance 1%; Manufacturer Part Number CRCW02014K70FNED
R59: 5.6K; RES-0201; Tolerance 1%; Manufacturer Part Number CRCW02015K60FNED
TP43, TP44, TP45: TP; TP-SMT

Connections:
/Charger-and-3.3V-Supply/RESET_SYS: Q45.4 (G2); also elsewhere on the board
/Hard-Disk/3V3_HDD_GATE: C12.2, C13.2, Q11.1 (G), R25.2, R27.1
/Hard-Disk/EN_3V3_HDD_L: Q45.6 (D1), R27.2
/Hard-Disk/EN_3V3_HDD_MPU_L: Q45.2 (S1); also elsewhere on the board
/Hard-Disk/IDE_CS0: J4.4; also elsewhere on the board
/Hard-Disk/IDE_CS1: J4.3; also elsewhere on the board
/Hard-Disk/IDE_DA0: J4.6; also elsewhere on the board
/Hard-Disk/IDE_DA1: J4.7; also elsewhere on the board
/Hard-Disk/IDE_DA2: J4.5; also elsewhere on the board
/Hard-Disk/IDE_DD0: J4.19; also elsewhere on the board
/Hard-Disk/IDE_DD1: J4.21; also elsewhere on the board
/Hard-Disk/IDE_DD2: J4.23; also elsewhere on the board
/Hard-Disk/IDE_DD3: J4.25; also elsewhere on the board
/Hard-Disk/IDE_DD4: J4.27; also elsewhere on the board
/Hard-Disk/IDE_DD5: J4.29; also elsewhere on the board
/Hard-Disk/IDE_DD6: J4.31; also elsewhere on the board
/Hard-Disk/IDE_DD7: J4.33; also elsewhere on the board
/Hard-Disk/IDE_DD8: J4.32; also elsewhere on the board
/Hard-Disk/IDE_DD9: J4.30; also elsewhere on the board
/Hard-Disk/IDE_DD10: J4.28; also elsewhere on the board
/Hard-Disk/IDE_DD11: J4.26; also elsewhere on the board
/Hard-Disk/IDE_DD12: J4.24; also elsewhere on the board
/Hard-Disk/IDE_DD13: J4.22; also elsewhere on the board
/Hard-Disk/IDE_DD14: J4.20; also elsewhere on the board
/Hard-Disk/IDE_DD15: J4.18; also elsewhere on the board
/Hard-Disk/IDE_DIOR_L: J4.13; also elsewhere on the board
/Hard-Disk/IDE_DIOW_L: J4.14; also elsewhere on the board
/Hard-Disk/IDE_DMACK_L: J4.9; also elsewhere on the board
/Hard-Disk/IDE_DMARQ: J4.16, R59.1; also elsewhere on the board
/Hard-Disk/IDE_INTRQ: J4.8, R53.1; also elsewhere on the board
/Hard-Disk/IDE_IORDY: J4.11, R56.2; also elsewhere on the board
/Hard-Disk/IDE_RESET_L: J4.35; also elsewhere on the board
/Hard-Disk/RESET_SYS_1V8_L: Q45.3 (D2), R22.2
/Hard-Disk/RESET_SYS_L: Q45.1 (G1); also elsewhere on the board
GND: C14.2, C58.2, J4.10, J4.12, J4.15, J4.17, J4.34, Q45.5 (S2), R53.2, R59.2; also elsewhere on the board
PP_1V8_SYS: R22.1; also elsewhere on the board
PP_3V3_HDD: C13.1, C14.1, C58.1, J4.1, J4.2, Q11.3 (D), R56.1, TP44.1, TP45.1; also elsewhere on the board
PP_3V3_SYS: C12.1, Q11.2 (S), R25.1, TP43.1; also elsewhere on the board

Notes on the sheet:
DESIGN NOTE: The Q45B's drain doesn't connect to anything outside of R22. Best guess is this is to bleed off charge from the capacitance distributed across PP_1V8_SYS to enforce rail sequencing. Either that or a legacy function stripped out from the 820-1763.
DD8
DD10
DD7
nDIOR/nHDMARDY/HSTROBE
DD5
DD11
DD13
GND
nDMACK
DD1
+3V3
DD9
DD2
DD6
DA1
nRESET
DD0
nCS0
nCS1
IORDY/nDMARDY/DSTROBE
INTRQ
DD3
nDIOW/STOP
DA0
DD15
DA2
DD14
DD12
DMARQ
DD4
